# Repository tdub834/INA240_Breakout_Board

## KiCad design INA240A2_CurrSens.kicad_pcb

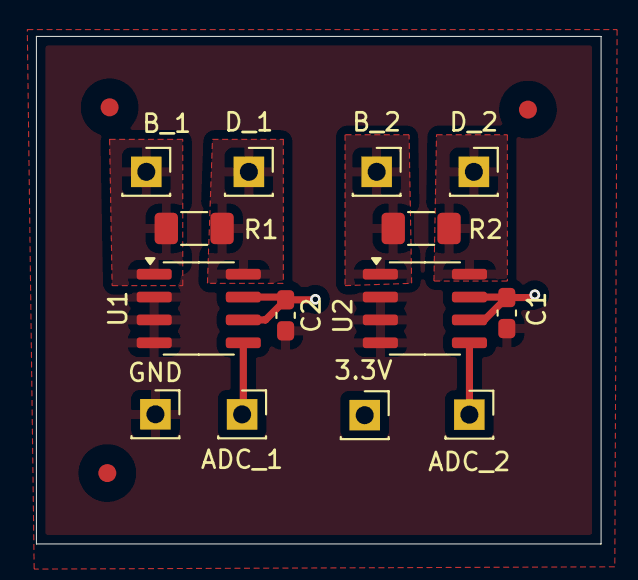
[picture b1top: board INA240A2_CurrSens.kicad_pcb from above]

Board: 2 copper layers, 31.4 x 28.2 mm, 17 parts (0 on the bottom side), 8 nets.

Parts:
3.3V: Conn_01x01_Pin; PinSocket_1x01_P2.54mm_Vertical
ADC_1, ADC_2: Conn_01x01_Pin; PinSocket_1x01_P2.54mm_Vertical
B_1, B_2: Conn_01x01_Pin; PinSocket_1x01_P2.54mm_Vertical
C1, C2: 0.1 uF; C_0603_1608Metric_Pad1.08x0.95mm_HandSolder
D_1, D_2: Conn_01x01_Pin; PinSocket_1x01_P2.54mm_Vertical
FID1, FID2, FID3: Fiducial; Fiducial_1mm_Mask3mm
GND: Conn_01x01_Pin; PinSocket_1x01_P2.54mm_Vertical
R1, R2: 0.05 ohms; R_1206_3216Metric_Pad1.30x1.75mm_HandSolder
U1, U2: INA240A2D; SOIC-8_3.9x4.9mm_P1.27mm

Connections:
+3.3V: 3.3V.1, C1.2, C2.2, U1.6 (V+), U1.7 (REF1), U2.6 (V+), U2.7 (REF1)
/ADC_1: ADC_1.1, U1.5
/ADC_2: ADC_2.1, U2.5
/BLDC_1: B_1.1, R1.2, U1.1 (-)
/BLDC_2: B_2.1, R2.2, U2.1 (-)
/Driver_1: D_1.1, R1.1, U1.8 (+)
/Driver_2: D_2.1, R2.1, U2.8 (+)
GND: C1.1, C2.1, GND.1, U1.2 (GND), U1.3 (REF2), U1.4 (GND), U2.2 (GND), U2.3 (REF2), U2.4 (GND)

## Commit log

2026-04-05 Initialized repo
2026-04-05 Added proper gitignore file
2026-04-05 Upload KiCad schematic and PCB layout
2026-04-06 added filled zones for voltage
2026-04-07 adjusted trace widths
2026-04-07 adjusted filled zones to correct drc
2026-04-07 adjusted board positioning to maintain signal integrity
2026-04-07 corrected layout pattern
